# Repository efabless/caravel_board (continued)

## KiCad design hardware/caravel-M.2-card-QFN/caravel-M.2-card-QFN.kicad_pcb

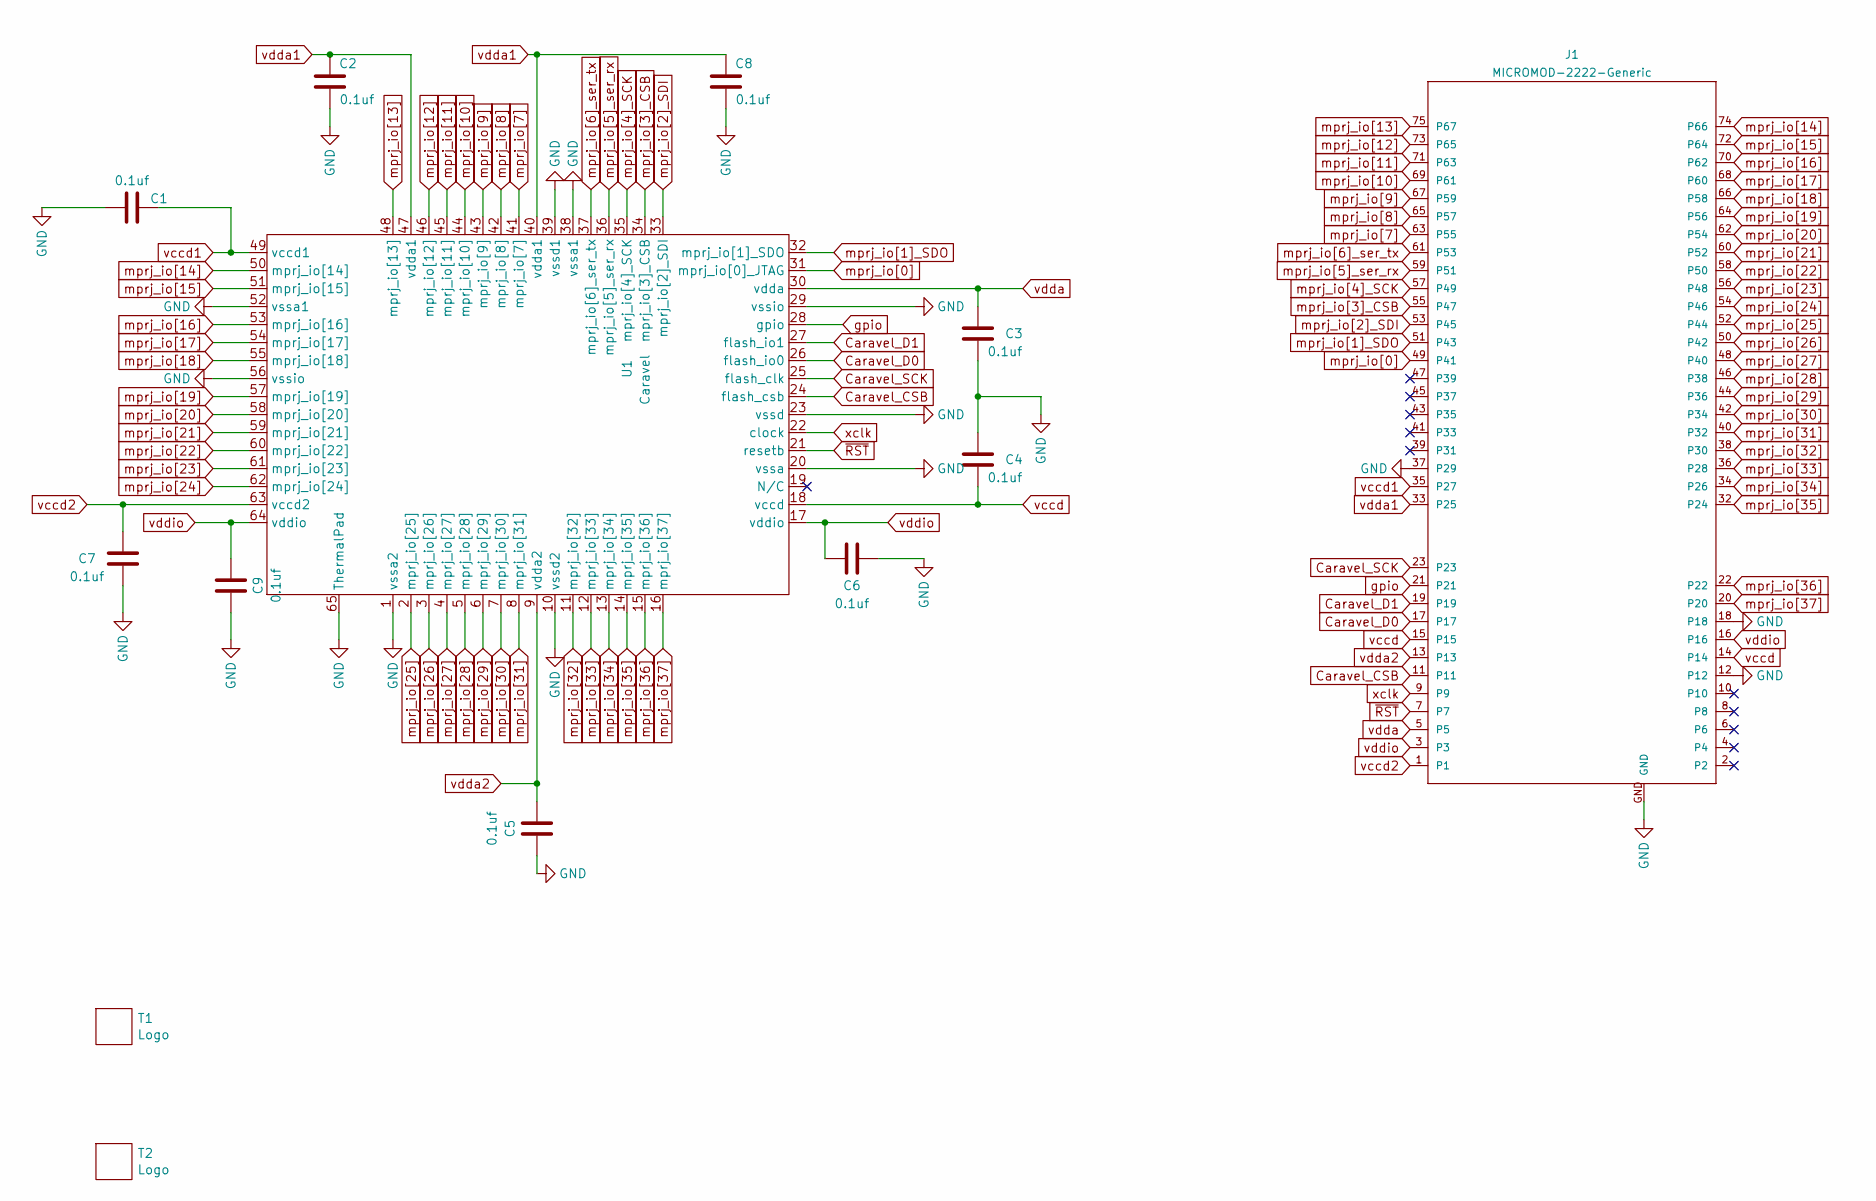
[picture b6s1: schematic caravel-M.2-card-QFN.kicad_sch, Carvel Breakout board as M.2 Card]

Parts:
C1, C2, C3, C4, C5, C6, C7, C8, C9: 0.1uf; C_0402_1005Metric
J1: MICROMOD-2222-Generic; MicroMod-M.2-CARD-E-22
T1: Logo; logo_small
T2: Logo; ef_logo
U1: Caravel; QFN-64-1EP_9x9mm_P0.5mm_EP7.65x7.65mm

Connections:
Caravel_CSB: J1.11, U1.24 (flash_csb)
Caravel_D0: J1.17, U1.26 (flash_io0)
Caravel_D1: J1.19, U1.27 (flash_io1)
Caravel_SCK: J1.23, U1.25 (flash_clk)
GND: C1.1, C2.2, C3.2, C4.1, C5.1, C6.1, C7.1, C8.2, C9.1, J1.12, J1.18, J1.37 (P29), J1.GND, U1.1 (vssa2), U1.10 (vssd2), U1.20 (vssa), U1.23 (vssd), U1.29 (vssio), U1.38 (vssa1), U1.39 (vssd1), U1.52 (vssa1), U1.56 (vssio), U1.65 (ThermalPad)
gpio: J1.21, U1.28 (gpio)
mprj_io[0]: J1.49 (P41), U1.31 (mprj_io[0]_JTAG)
mprj_io[1]_SDO: J1.51 (P43), U1.32 (mprj_io[1]_SDO)
mprj_io[2]_SDI: J1.53 (P45), U1.33 (mprj_io[2]_SDI)
mprj_io[3]_CSB: J1.55 (P47), U1.34 (mprj_io[3]_CSB)
mprj_io[4]_SCK: J1.57 (P49), U1.35 (mprj_io[4]_SCK)
mprj_io[5]_ser_rx: J1.59 (P51), U1.36 (mprj_io[5]_ser_rx)
mprj_io[6]_ser_tx: J1.61 (P53), U1.37 (mprj_io[6]_ser_tx)
mprj_io[7]: J1.63 (P55), U1.41 (mprj_io[7])
mprj_io[8]: J1.65 (P57), U1.42 (mprj_io[8])
mprj_io[9]: J1.67 (P59), U1.43 (mprj_io[9])
mprj_io[10]: J1.69 (P61), U1.44 (mprj_io[10])
mprj_io[11]: J1.71 (P63), U1.45 (mprj_io[11])
mprj_io[12]: J1.73 (P65), U1.46 (mprj_io[12])
mprj_io[13]: J1.75 (P67), U1.48 (mprj_io[13])
mprj_io[14]: J1.74 (P66), U1.50 (mprj_io[14])
mprj_io[15]: J1.72 (P64), U1.51 (mprj_io[15])
mprj_io[16]: J1.70 (P62), U1.53 (mprj_io[16])
mprj_io[17]: J1.68 (P60), U1.54 (mprj_io[17])
mprj_io[18]: J1.66 (P58), U1.55 (mprj_io[18])
mprj_io[19]: J1.64 (P56), U1.57 (mprj_io[19])
mprj_io[20]: J1.62 (P54), U1.58 (mprj_io[20])
mprj_io[21]: J1.60 (P52), U1.59 (mprj_io[21])
mprj_io[22]: J1.58 (P50), U1.60 (mprj_io[22])
mprj_io[23]: J1.56 (P48), U1.61 (mprj_io[23])
mprj_io[24]: J1.54 (P46), U1.62 (mprj_io[24])
mprj_io[25]: J1.52 (P44), U1.2 (mprj_io[25])
mprj_io[26]: J1.50 (P42), U1.3 (mprj_io[26])
mprj_io[27]: J1.48 (P40), U1.4 (mprj_io[27])
mprj_io[28]: J1.46 (P38), U1.5 (mprj_io[28])
mprj_io[29]: J1.44 (P36), U1.6 (mprj_io[29])
mprj_io[30]: J1.42 (P34), U1.7 (mprj_io[30])
mprj_io[31]: J1.40 (P32), U1.8 (mprj_io[31])
mprj_io[32]: J1.38 (P30), U1.11 (mprj_io[32])
mprj_io[33]: J1.36 (P28), U1.12 (mprj_io[33])
mprj_io[34]: J1.34 (P26), U1.13 (mprj_io[34])
mprj_io[35]: J1.32 (P24), U1.14 (mprj_io[35])
mprj_io[36]: J1.22, U1.15 (mprj_io[36])
mprj_io[37]: J1.20, U1.16 (mprj_io[37])
vccd: C4.2, J1.14, J1.15, U1.18 (vccd)
vccd1: C1.2, J1.35 (P27), U1.49 (vccd1)
vccd2: C7.2, J1.1, U1.63 (vccd2)
vdda: C3.1, J1.5, U1.30 (vdda)
vdda1: C2.1, C8.1, J1.33 (P25), U1.40 (vdda1), U1.47 (vdda1)
vdda2: C5.2, J1.13, U1.9 (vdda2)
vddio: C6.2, C9.2, J1.3, J1.16, U1.17 (vddio), U1.64 (vddio)
xclk: J1.9, U1.22 (clock)
~RST: J1.7, U1.21 (resetb)

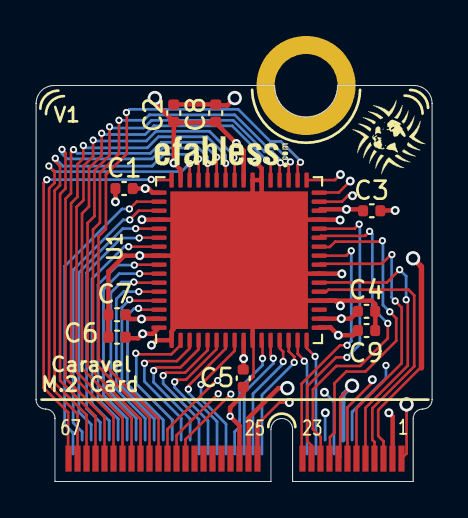
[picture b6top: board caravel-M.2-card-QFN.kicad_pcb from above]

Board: 4 copper layers, 22.0 x 22.0 mm, 13 parts (0 on the bottom side), 53 nets.

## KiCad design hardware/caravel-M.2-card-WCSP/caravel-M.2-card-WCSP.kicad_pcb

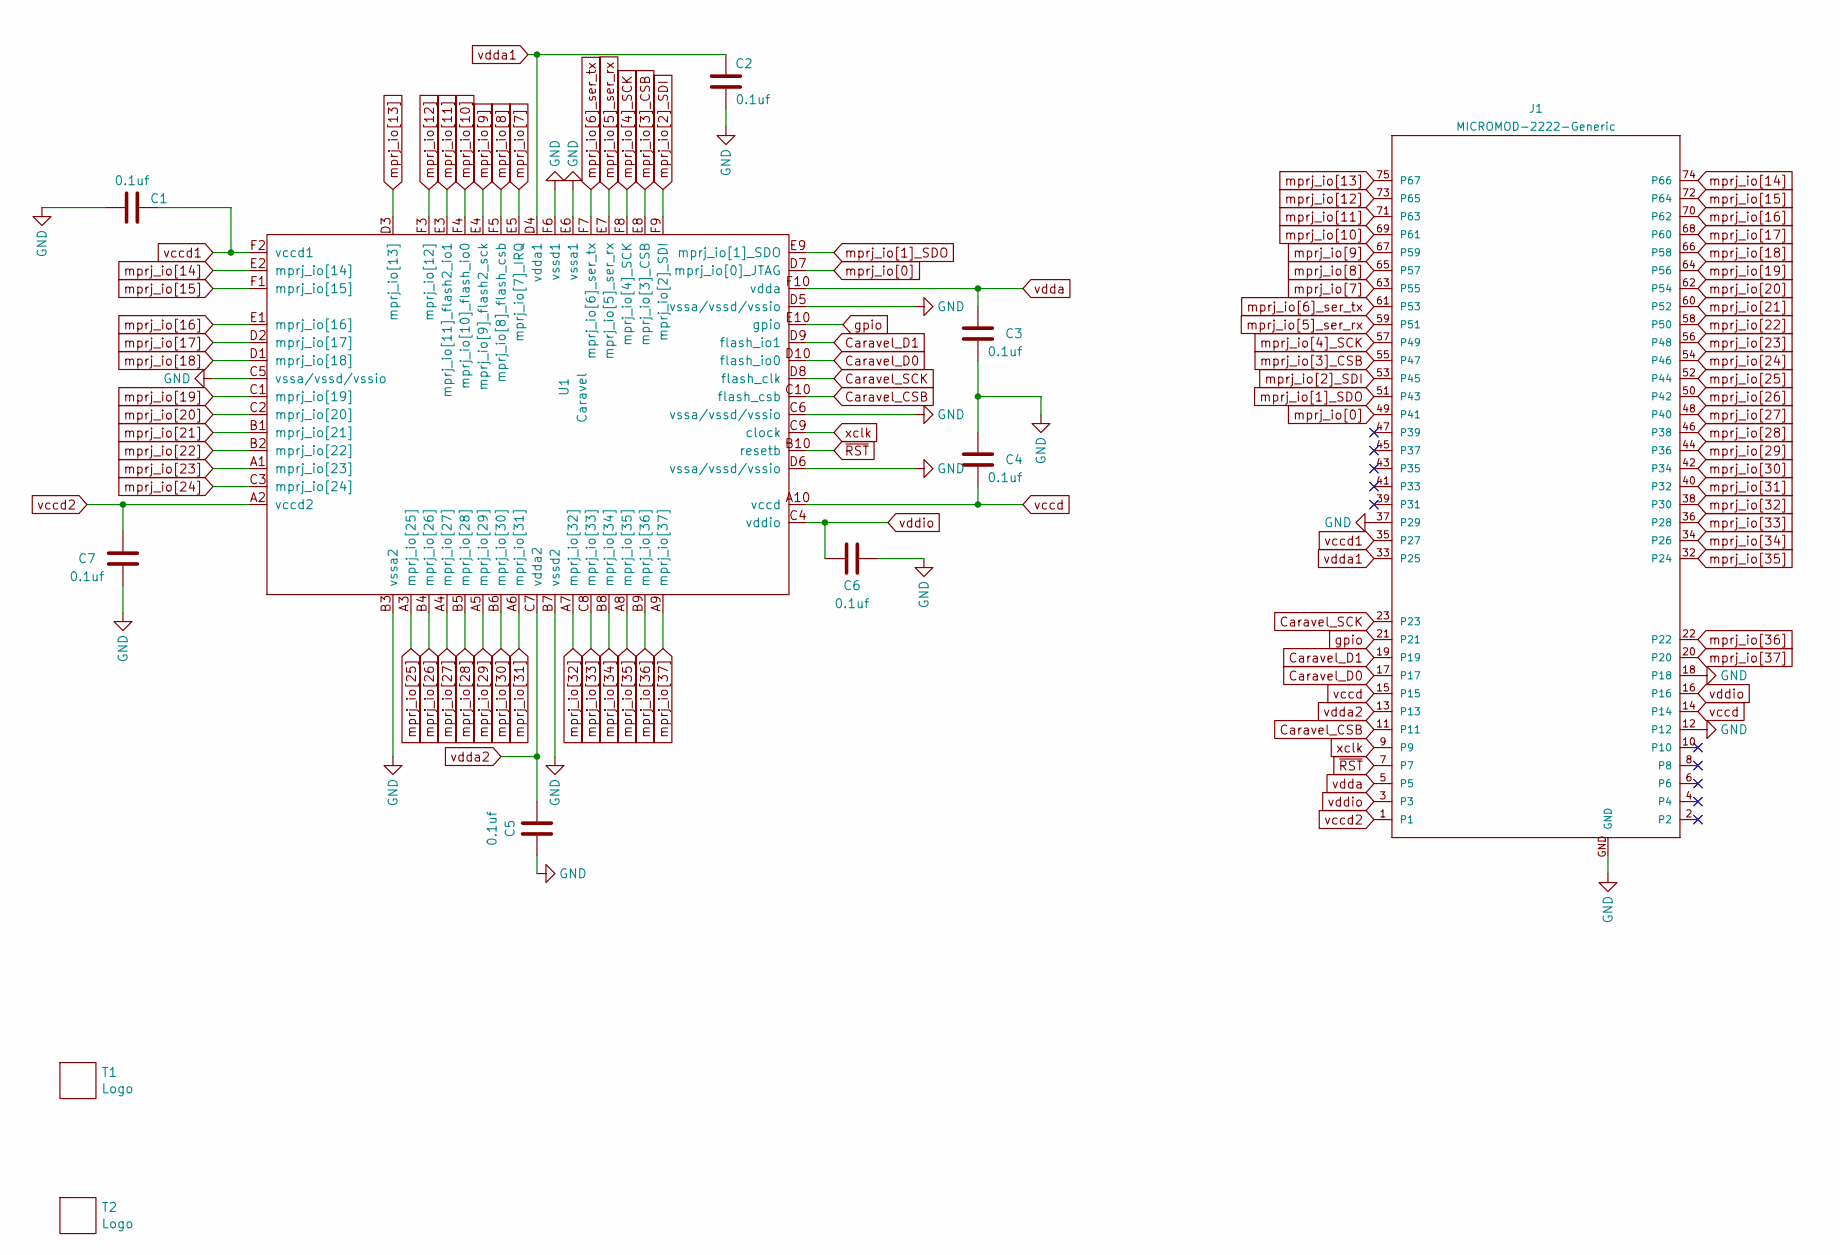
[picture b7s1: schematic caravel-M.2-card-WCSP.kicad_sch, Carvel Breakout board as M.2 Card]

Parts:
C1, C2, C3, C4, C5, C6, C7: 0.1uf; C_0402_1005Metric
J1: MICROMOD-2222-Generic; MicroMod-M.2-CARD-E-22
T1: Logo; logo_small
T2: Logo; ef_logo
U1: Caravel; Caravel_WCSP

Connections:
Caravel_CSB: J1.11, U1.C10 (flash_csb)
Caravel_D0: J1.17, U1.D10 (flash_io0)
Caravel_D1: J1.19, U1.D9 (flash_io1)
Caravel_SCK: J1.23, U1.D8 (flash_clk)
GND: C1.1, C2.2, C3.2, C4.1, C5.1, C6.1, C7.1, J1.12, J1.18, J1.37 (P29), J1.GND, U1.B3 (vssa2), U1.B7 (vssd2), U1.C5 (vssa/vssd/vssio), U1.C6 (vssa/vssd/vssio), U1.D5 (vssa/vssd/vssio), U1.D6 (vssa/vssd/vssio), U1.E6 (vssa1), U1.F6 (vssd1)
gpio: J1.21, U1.E10 (gpio)
mprj_io[0]: J1.49 (P41), U1.D7 (mprj_io[0]_JTAG)
mprj_io[1]_SDO: J1.51 (P43), U1.E9 (mprj_io[1]_SDO)
mprj_io[2]_SDI: J1.53 (P45), U1.F9 (mprj_io[2]_SDI)
mprj_io[3]_CSB: J1.55 (P47), U1.E8 (mprj_io[3]_CSB)
mprj_io[4]_SCK: J1.57 (P49), U1.F8 (mprj_io[4]_SCK)
mprj_io[5]_ser_rx: J1.59 (P51), U1.E7 (mprj_io[5]_ser_rx)
mprj_io[6]_ser_tx: J1.61 (P53), U1.F7 (mprj_io[6]_ser_tx)
mprj_io[7]: J1.63 (P55), U1.E5 (mprj_io[7]_IRQ)
mprj_io[8]: J1.65 (P57), U1.F5 (mprj_io[8]_flash_csb)
mprj_io[9]: J1.67 (P59), U1.E4 (mprj_io[9]_flash2_sck)
mprj_io[10]: J1.69 (P61), U1.F4 (mprj_io[10]_flash_io0)
mprj_io[11]: J1.71 (P63), U1.E3 (mprj_io[11]_flash2_io1)
mprj_io[12]: J1.73 (P65), U1.F3 (mprj_io[12])
mprj_io[13]: J1.75 (P67), U1.D3 (mprj_io[13])
mprj_io[14]: J1.74 (P66), U1.E2 (mprj_io[14])
mprj_io[15]: J1.72 (P64), U1.F1 (mprj_io[15])
mprj_io[16]: J1.70 (P62), U1.E1 (mprj_io[16])
mprj_io[17]: J1.68 (P60), U1.D2 (mprj_io[17])
mprj_io[18]: J1.66 (P58), U1.D1 (mprj_io[18])
mprj_io[19]: J1.64 (P56), U1.C1 (mprj_io[19])
mprj_io[20]: J1.62 (P54), U1.C2 (mprj_io[20])
mprj_io[21]: J1.60 (P52), U1.B1 (mprj_io[21])
mprj_io[22]: J1.58 (P50), U1.B2 (mprj_io[22])
mprj_io[23]: J1.56 (P48), U1.A1 (mprj_io[23])
mprj_io[24]: J1.54 (P46), U1.C3 (mprj_io[24])
mprj_io[25]: J1.52 (P44), U1.A3 (mprj_io[25])
mprj_io[26]: J1.50 (P42), U1.B4 (mprj_io[26])
mprj_io[27]: J1.48 (P40), U1.A4 (mprj_io[27])
mprj_io[28]: J1.46 (P38), U1.B5 (mprj_io[28])
mprj_io[29]: J1.44 (P36), U1.A5 (mprj_io[29])
mprj_io[30]: J1.42 (P34), U1.B6 (mprj_io[30])
mprj_io[31]: J1.40 (P32), U1.A6 (mprj_io[31])
mprj_io[32]: J1.38 (P30), U1.A7 (mprj_io[32])
mprj_io[33]: J1.36 (P28), U1.C8 (mprj_io[33])
mprj_io[34]: J1.34 (P26), U1.B8 (mprj_io[34])
mprj_io[35]: J1.32 (P24), U1.A8 (mprj_io[35])
mprj_io[36]: J1.22, U1.B9 (mprj_io[36])
mprj_io[37]: J1.20, U1.A9 (mprj_io[37])
vccd: C4.2, J1.14, J1.15, U1.A10 (vccd)
vccd1: C1.2, J1.35 (P27), U1.F2 (vccd1)
vccd2: C7.2, J1.1, U1.A2 (vccd2)
vdda: C3.1, J1.5, U1.F10 (vdda)
vdda1: C2.1, J1.33 (P25), U1.D4 (vdda1)
vdda2: C5.2, J1.13, U1.C7 (vdda2)
vddio: C6.2, J1.3, J1.16, U1.C4 (vddio)
xclk: J1.9, U1.C9 (clock)
~RST: J1.7, U1.B10 (resetb)

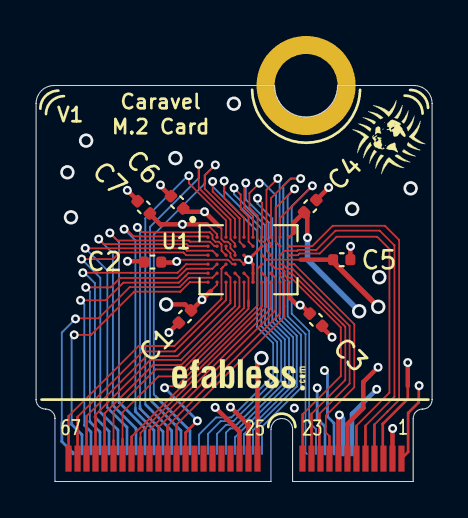
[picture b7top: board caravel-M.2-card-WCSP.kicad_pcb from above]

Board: 4 copper layers, 22.0 x 22.0 mm, 11 parts (0 on the bottom side), 53 nets.

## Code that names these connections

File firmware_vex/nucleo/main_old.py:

from machine import Pin, SPI, SoftSPI, sleep, SoftI2C, reset
from pyb import LED, Timer
from time import sleep
from i2c import I2C
from main import choose_test, Gpio

class prog_supply:
    
    def __init__(self):
        self.scl = Pin('I2C2_SCL', mode=Pin.OPEN_DRAIN, pull=Pin.PULL_UP, value=1)
        self.sda = Pin('I2C2_SDA', mode=Pin.OPEN_DRAIN, pull=Pin.PULL_UP, value=1)
        self.i2c = I2C(scl=self.scl, sda=self.sda)
        self.i2c.init()
        
    def read_1v8(self):
        self.i2c.write_byte(0x50, start=True, stop=False)
        self.i2c.write_byte(0x0c, start=False, stop=False)
        self.i2c.write_byte(0x51, start=True, stop=False)
        value = self.i2c.read_byte(ack=True, stop=False) << 8
        value |= self.i2c.read_byte(ack=False, stop=True)
        return value
    
    def write_1v8(self, value):
        self.i2c.write_byte(0x50, start=True, stop=False)
        self.i2c.write_byte(0x10 & value >> 8, start=False, stop=False)
        ack = self.i2c.write_byte(value & 0xff, start=False, stop=True)
        return ack

    def read_3v3(self):
        self.i2c.write_byte(0x50, start=True, stop=False)
        self.i2c.write_byte(0x1c, start=False, stop=False)
        self.i2c.write_byte(0x51, start=True, stop=False)
        value = self.i2c.read_byte(ack=True, stop=False) << 8
        value |= self.i2c.read_byte(ack=False, stop=True)
        return value

    def write_3v3(self, value):
        self.i2c.write_byte(0x50, start=True, stop=False)
        self.i2c.write_byte(0x10 | (value >> 8), start=False, stop=False)
        ack = self.i2c.write_byte(value & 0xff, start=False, stop=True)
        return ack


def read_io_all():
    v = 0
    for i in range(38):
        v = v << 1
        v |= io[i].value() & 0x01
    return v


def write_io_all(v):
    for i in range(38):
        io[i].value(v)


io = []


def setup_io():
    for x in range(38):
        # io.append(Pin('IO_'+str(x), mode=Pin.OUT))
        io.append(Pin('IO_' + str(x), mode=Pin.IN, pull=None))

class Test:
    test_name = "junk"

# -----------------------------------


rst = Pin('MR', mode=Pin.OUT, value=1)
en_1v8 = Pin('EN_VOUT1', mode=Pin.OUT, value=1)
en_3v3 = Pin('EN_VOUT2', mode=Pin.OUT, value=1)

# setup user LEDs
#led_green = LED(1)
#led_blue = LED(2)
#led_red = LED(3)

#pb5 = Pin('TIM3_CH2', mode=Pin.OUT)
#tim = Timer(3, freq=10_000_000)
#ch = tim.channel(2, mode=Timer.PWM, pin=pb5)
#ch.pulse_width_percent(50)
    
#tim.init(period=1, callback=timer_callback)
#pb5.on()
#pwm = PWM(pb5)
#pwm.init(freq=1000000, duty_ns=500)

#for x in range(2):
#    sleep(0.3)
#    led_red.toggle()
#    led_green.toggle()
#    led_blue.toggle()

sleep(2)

ps = prog_supply()
#ps.write_1v8(0x1f)  #1.6V
ps.write_1v8(0x11)  #1.7V
#ps.write_1v8(0x0b)  #1.8V
ps.write_3v3(0x3a)
print("1v8 = {}".format(hex(ps.read_1v8())))
print("3v3 = {}".format(hex(ps.read_3v3())))

rst.off()
sleep(1)
en_1v8.off()
en_3v3.off()
sleep(1)
en_3v3.on()
en_1v8.on()
sleep(1)

#check()

reset()
flash("blink.hex")

rst.on()

#setup_io()

#gpio_l = Gpio()
#gpio_h = Gpio()
#start_time = 0
#test = {}
#test = Test()

#choose_test(test, "config_io_o_l", gpio_l, gpio_h, start_time, "junk")

print("\nRunning...")

while False:
    #sleep(0.5)
    #print(".")
    #led_green.toggle()
    # write_io_all(1)
#    _data = "{:038b}".format(read_io_all())
    data = ""
    for x in _data:
        data = x + data
#    print("{} {} {} {} {} {} {} {} {} {}".format(\
#        data[0:4],data[4:8],data[8:12],data[12:16],data[16:20],data[20:24],data[24:28],data[28:32],data[32:36],data[36:38]))
    #sleep(0.5)
    #print(".")
    #led_green.toggle()
    # write_io_all(0)
    #print(bin(read_io_all()))

print("Done.")

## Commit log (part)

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2022-08-26 further updates, correction for data dependent holds, 8 gpio working on upper IO.
2022-08-26 add hkdebug for vex
2022-08-26 update caravel breakout board symbol
2022-08-26 add caravel FTDI mainboard V4 (Rev 4A)
2022-08-31 gpio configuration working for 18 IO on part F1 - 7
2022-08-31 remove mprj_bitbang hex files
2022-08-31 add Caravel_breakout_v2 files
2022-09-01 IO configuration for part F1-7
2022-09-01 update caravel FTDI mainboard V4 (Rev 4B)
2022-09-01 add wip of caravel board compatible with Nucleo
2022-09-02 add Matt test
2022-09-06 Matt RGB test working
2022-09-08 update caravel FTDI mainboard V4 (Rev 4B) to support different LDO devices with the same footprint
2022-09-08 update BOM caravel FTDI mainboard V4 (Rev 4B)
2022-09-08 [in review] update caravel board Nucleo-144 hat
2022-09-12 update caravel board Nucleo-144 hat
2022-09-16 update caravel nucleo hat board Rev A
2022-09-18 add Nucleo firmware directory
2022-09-30 nucleo support for flashing caravel
2022-10-02 update MCP4661 symbol (QFN Package)
2022-10-02 update caravel nucleo hat board Rev A PCB
2022-10-03 nucleo turn-on testing
2022-10-04 update caravel QFN breakout board with WCSP pinout (V2)
2022-10-12 add gerber files
2022-11-04 update matt test for pwm demo
2022-11-07 update nucleo sw
2022-11-07 first itteration to change from python to micropython
2022-11-07 added API for nucleo
2022-11-07 expand nucleo partition
2022-11-08 add bitstream.mpy
2022-11-08 iteration of fixes
2022-11-08 updated gpio_config_builder.py
2022-11-08 update nucleo
2022-11-10 update flash to include flash_mem and erase
2022-11-10 add boot.py
2022-11-11 Makefile
2022-11-13 expand partition
2022-11-13 update gpio_config_builder.py and gpio_config_io.c to not generate n_bits value
2022-11-13 modified hex files
2022-11-13 removed bak files
2022-11-13 iteration for fixing io_config.py
2022-11-13 fixed flash script
2022-11-13 fix flash_mem()
2022-11-14 fix io_config.py - hex file read to find addr
2022-11-14 io_config data_flash()
2022-11-14 fixing bug with io_config.py
2022-11-16 update flash.py to handle previous stopped execution
2022-11-16 added gpio_config_data.c
2022-11-16 fixed send_packet.c
2022-11-16 first itteration of debugging flash: writing to new file
2022-11-16 added hex files
2022-11-16 added support for gpio_mgmt
2022-11-17 nucleo_firmware.hex adds GPIO_MGMT pin
2022-11-17 added flash_2
2022-11-17 changed timeout to accurate delay)
2022-11-17 changes in hex and algorithm
2022-11-17 changes to the builder
2022-11-17 correct firmware for position of n_bits
2022-11-18 fixed config_io_o_l/h c files
2022-11-18 update config_io_o to pad to fixed length
2022-11-20 change protocol to remove timing dependency
2022-11-20 changed protocol to only use 1 hex file and modified the script to output the correct file format in the nucleo
2022-11-20 LEDs turn on when running
2022-11-20 nucleo - add led indicators
2022-11-20 nucleo - tweak configuration file and repl runtime output
2022-11-21 update led, outputs, nucleo firmware
2022-11-21 remove mpy-cross
2022-11-21 add README.md for nucleo
2022-11-22 update final summary
2022-11-23 update output
2022-11-30 add sleep for nucleo
2022-12-21 Update README.md
    add the QFN breakout
2022-12-22 update gpio_config and Matt's example
2022-12-23 correct path for import
2022-12-23 fix simulator, add gpio checker
2023-01-19 firmware_vex/nucleo: fix typo
2023-01-19 add counter example firmware
2023-01-19 Adding ttyACM0 variant
2023-01-19 Fixed typo
2023-01-20 Remove redundant cd instruction
2023-01-20 Include instructions to get your correct device.
2023-01-20 Move cd to before run command.
2023-01-21 Remove space in SED_CMD edit in place suffix
    No `.orig` backup file is generated with that space.
2023-01-27 add targets for nucleo hat power and flash
2023-01-27 add check for nucleo volume
2023-01-27 automatically set device
2023-01-27 add sanity check
2023-01-27 fix sanity check typo
2023-01-27 correct Makefile issue with check_device
2023-01-28 update gpio_test
2023-01-28 Fixing sed command
    On Ubuntu 21.10 sed needs the parameter for the -i to be attached directly without a space in between
    Adding additional TOOLCHAIN path
2023-01-28 added comment
2023-01-28 update gpio_test directory
2023-01-28 update gpio_config
2023-01-28 update sanity check
2023-01-29 update sanity check summary
2023-01-30 correct checker
2023-01-30 initial commit to new protocol with handshake on io[0] and io[37]
2023-01-30 add release_pins()
2023-01-30 update Makefile for counter_proj_example
2023-01-30 update documentation
2023-01-30 fix typo in README
2023-02-01 increased pulse width
2023-02-01 changed timout to accurate us
2023-02-01 fixed reconfiguration
2023-02-01 update poweron target
2023-02-02 correct IO[37] and add poweron() for io_config.py
2023-02-02 add version recorded in gpio_config_def.py
2023-02-02 README for gpio_config
2023-02-02 \+ config_mode in Test() object to specify in io[37] should be initialized as input or output \+ turn_off_ios() to turn all ios off after configuration is done \~ implicitly turn off the board by wri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
2023-02-02 fixed bug with sanity check
2023-02-02 added led toggling that was removed in previous protocol itteration
2023-02-02 added sync command after cp to insure no fs corruption
2023-02-02 added voltage control in make run and make sanity_check
2023-02-02 fix voltage on poweron()
2023-02-02 add continuous voltage support for 1.8V supply
2023-02-02 parameterize copy command in Makefile
2023-02-03 correct power sequence; remove turn_off_ios()
2023-02-04 fix fun_flash_caravel()
2023-02-04 correct IO[37]
2023-02-04 updated hex file with IO config
2023-02-04 update firmware to swap IO 0 & 37
2023-02-04 bypass IO[1] for analog
2023-02-04 add VOLTAGE for run_analog
2023-02-04 fix run target
2023-02-04 add logic to change IO[1] from INDEPENDENT to DEPENDENT
2023-02-05 changed channels tested for analog
2023-02-06 changed summary for analog test
2023-02-06 documented io_config.py
2023-02-06 added LED class in nucleo_api()
2023-02-06 update Makefile for matt_test
2023-02-08 add missing photo
2023-02-09 added flowchart and functions documentation
2023-02-09 added flowchart png
2023-02-09 automatically set voltage from local gpio_config_def.py for make poweron and make flash_nucleo
2023-02-15 v1.2.1 -- add support for make change_power VOLTAGE=<v>
2023-02-16 add jupyter notebooks for documenting bringup
2023-03-09 add Sparkfun-MicroMod Eagle lib converted to KiCad
2023-03-20 add caravel breakout board as M.2 card (V1)
2023-03-23 ~ rename `caravel-M.2-card-WCSP` for caravel breakout M.2 card as the caravel package is WCSP
2023-03-23 ~ update M.2 connector footprint ~ update old strive footprints as they produced some DRC errors
2023-03-23 + add caravel M.2 carrier board (REV 5A) that is compatible with caravel M.2 card
2023-03-27 update Caravel M.2 card PCB + add large via for each power domain to ease monitoring them
2023-03-28 rename caravel M.2 carrier board to caravel dev v5 board update Caravel dev (REV5A) pcb: ~ update the serial display connector to 3-pin + add large via for the manual reset to be able to monitor it
2023-03-28 add gerber files for Caravel dev (REV5A) and M.2 card pcbs
2023-03-28 add datasheets for M.2 connector and screw standoff
2023-03-28 update `caravel-dev-v5-M.2` BOM with M.2 connector
2023-04-03 add QFN caravel breakout board as M.2 card (V1)
2023-04-03 ~ update Sparkfun MicroMod footprint with copper fill keepout area near the card edge this is required to avoid shorts when the card is inserted into the connector
2023-04-03 add caravel Nucleo hat PCB that utilizes M.2 connector (REV 2A)
2023-04-04 hardware/caravel_Nucleo: render text in schematic
2023-04-05 update `caravel-Nucleo-v2-M.2` BOM
2023-04-05 add LED bar pcb for caravel demo project
2023-04-09 update `led-bar-pcb` BOM with jumpers
2023-04-12 update `led-bar-pcb` BOM with resistors part
2023-04-14 + add `caravel-M.2-card-QFN` pcb BOM
2023-04-17 ~ fix `caravel-M.2-card-QFN` BOM caps quantity
2023-05-02 add 5V oscillator footprint
2023-05-02 add 5V development board (REV 6A) BOM and schematic
2023-05-03 add 5V development board (REV 6A) PCB and gerbers
2023-05-03 render 5V dev Board schematic pdf
2023-05-03 add stanford directory and README
2023-05-04 update for stanford projects
2023-05-04 test datasheet
2023-05-04 add caravel_datasheet.md
2023-05-05 fix sed
2023-05-05 caravel_datasheet.md
2023-05-05 update Makefile
2023-05-05 add print functions
2023-05-11 add missing file for gf180
2023-05-15 update 5V development board (REV 6B) schematic: ~ fix the reversed connections on the U10 level shifter + add 1 and 0.01 uF bypass caps to the Flash memory supply + add 10 uF bulk decoupling cap to t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
2023-05-25 update `caravel-5V-dev-v6-M.2` to REV6B that fixes identified issues during bringup
2023-05-26 update `caravel-5V-dev-v6-M.2` (REV6B) + add an 0.1uF bypass cap to the Flash level shifters ~ update BOM
2023-06-12 gf180 blink hex file
2023-06-13 add README for firmware_vex
2023-06-13 update README.md with QR code
2023-06-13 README.md
2023-07-02 Improve flasher script compatibility
    Adds support for hex files generated by `bincopy` with `verilog_vmem` output format.
    The `bincopy` python package includes the address at the beginning of each line, e.g.:
    ```
    @00000000 B7 00 00 10 67 80 80 00 73 50 40 30 73 50 40 34 93 00 00 00 13 01 00 00 93 01 00 00 13 02 00 00
    @00000020 93 02 00 00 13 03 00 00 93 03 00 00 13 04 00 00 93 04 00 00 93 06 00 00 13 07 00 00 93 07 00 00
    @00000040 13 08 00 00 93 08 00 00 13 09 00 00 93 09 00 00 13 0A 00 00 93 0A 00 00 13 0B 00 00 93 0B 00 00
2023-07-03 gf180/README: fix makefile path
2023-07-04 Fixed writing small sections that may overlap page boundaries
2023-07-20 Updated compiler architecture
2023-07-31 Fixed writing unaligned sections that may overlap page boundaries of SPI-flash (GF180)
2023-08-01 update directory structure
2023-08-04 update ARCH tag
2023-08-06 Added architecture detection
2023-08-21 Corrected the assignments for GPIO pull-up and pull-down input modes to match the values in the caravel repository.
2023-09-25 broken links
2023-09-25 qfn link
2023-09-25 update qr
2023-09-25 abs link
2023-09-25 fix links, add bullets to the commands at the end
2023-10-07 add gerbers for panelized breakout; reorganize hardware directories
2024-01-15 add caravel_projectid.py
2024-01-16 fix typo in binary reversal of project id
2024-01-25 add caravel
2024-01-25 add caravel_registers.pdf
2024-01-30 webinar demos
2024-01-30 default toolpath
2024-01-31 + add TMUX4053 and DS1086LU symbols and footprints
2024-01-31 + add clear dev board schematic and BOM
2024-01-31 ~ update clear PCB with test pads for clock generator dither enable and power-down mode enable to allow enabling them if needed
2024-01-31 ~ update clear dev board schematic pdf
2024-02-05 ~ update buffer symbol
2024-02-05 + add a tri-state buffer to connect `MEM_SO` to `USB_SI` only when the FTDI is programming the Flash
2024-02-08 update clear dev BOM
2024-02-08 + add clear dev board gerbers and Fab drawing
2024-02-12 ~ update caravel v5 board: ~ fix UART mode issue by enabling it by default (pull `~UART_EN` down) and in SPI mode, the FTDI drives `~UART_EN` high. This is required since the FTDI GPIOs are not confi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
2024-02-12 ~ update caravel v5 REV5B BOM
2024-02-28 ~ update caravel REV5B board files
2024-02-28 ~ update footprints
2024-03-03 ~ update caravel REV5B
2024-03-03 ~ update BOM caravel REV5B
2024-03-03 ~ update logos to include F.Fab layer drawings for fabrication drawings files
2024-03-03 add caravel REV5B Fab drawing
2024-03-05 ~ update caravel REV 5B PCB
2024-03-06 ~ update Fab drawing of caravel REV 5B
2024-03-10 + add larger logos footprints
2024-03-10 ~ update caravel REV 5B with larger logos
2024-03-10 ~ update caravel REV 5B fab drawing
2024-04-01 serial client for blink test
2024-04-21 update clear dev board to REV 1B after layout review
2024-04-22 update clear board REV 1B fab drawing
2024-04-22 update clear board REV 1B
2024-07-02 HKDebug cleanup fixes: Restore UART enable per each script; fix minor bugs
